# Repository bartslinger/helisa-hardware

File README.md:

# helisa-hardware
Extension boards for the  "open source" autopilot.

## Lisa/SD
SD Card slot replaces superbit. Has pads to solder deltang R31 module (for RC).

## LisaShield
Easy connectors for Walkera Genius CP V2. Includes pads for Bluetooth transceiver which can be switched on/off by a slider. Solder bridge is available for permenent on.

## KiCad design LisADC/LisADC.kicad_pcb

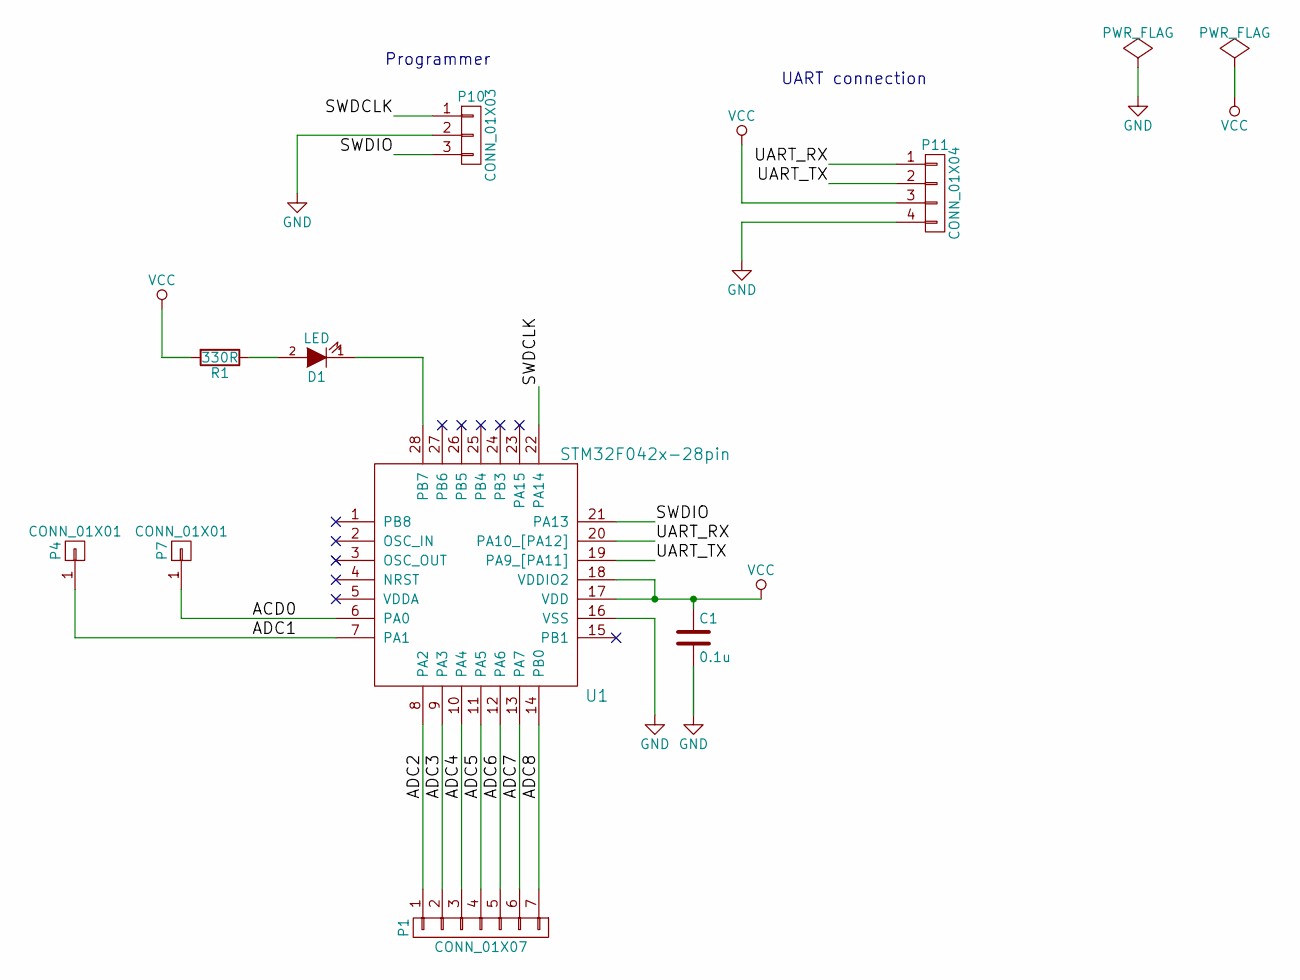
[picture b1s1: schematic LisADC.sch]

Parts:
C1: 0.1u; C_0603
D1: LED; LED-0603
P1: CONN_01X07; 7x1_1.27mm
P4, P7: CONN_01X01; 1x1_1.27mm
P10: CONN_01X03; 3x1_1.27mm
P11: CONN_01X04; 4x1_1.27mm
R1: 330R; R_0603
U1: STM32F042x-28pin; UFQFPN28

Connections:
/ACD0: P7.1, U1.6 (PA0)
/ADC1: P4.1, U1.7 (PA1)
/ADC2: P1.1, U1.8 (PA2)
/ADC3: P1.2, U1.9 (PA3)
/ADC4: P1.3, U1.10 (PA4)
/ADC5: P1.4, U1.11 (PA5)
/ADC6: P1.5, U1.12 (PA6)
/ADC7: P1.6, U1.13 (PA7)
/ADC8: P1.7, U1.14 (PB0)
/SWDCLK: P10.1, U1.22 (PA14)
/SWDIO: P10.3, U1.21 (PA13)
/UART_RX: P11.1, U1.20 (PA10_[PA12])
/UART_TX: P11.2, U1.19 (PA9_[PA11])
GND: C1.2, P10.2, P11.4, U1.16 (VSS)
unnamed: D1.1 (K), U1.28 (PB7)
unnamed: D1.2 (A), R1.1
VCC: C1.1, P11.3, R1.2, U1.17 (VDD), U1.18 (VDDIO2)

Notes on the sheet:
UART connection
Programmer

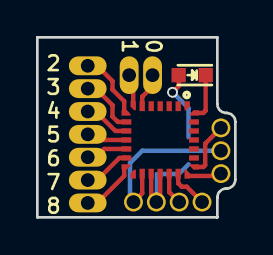
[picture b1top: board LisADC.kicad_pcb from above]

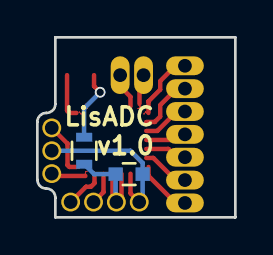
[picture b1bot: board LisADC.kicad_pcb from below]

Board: 2 copper layers, 11.0 x 10.0 mm, 9 parts (2 on the bottom side), 17 nets.

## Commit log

2015-10-05 Version 1.0 submitted for production
2015-12-15 ADC to UART conversion board for Lisa/S
